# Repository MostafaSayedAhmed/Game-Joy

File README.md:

# Game-Joy
The Project is game console i call it Game Joy that contain two games: Snake Game and Jumping Game ( Like Google Dino)

The Project consist of 3 Part :
- Code :
it contain implementation of both jumping game and snake game where an external interrupt is used to start game at menu and an external button is used to switch between the 2 games

- Hardware Design :
The board is designed using Eagle with documentation about the function of each button

- Simulation:
The whole project is simulated using proteus which is used to check bugs and glitches

Components Used:
- ATMEGA328P
- LCD
- 4 Switches
- Battery
- one 220 ohm resistor

Skills Used :
- Problem Solving
- Coding

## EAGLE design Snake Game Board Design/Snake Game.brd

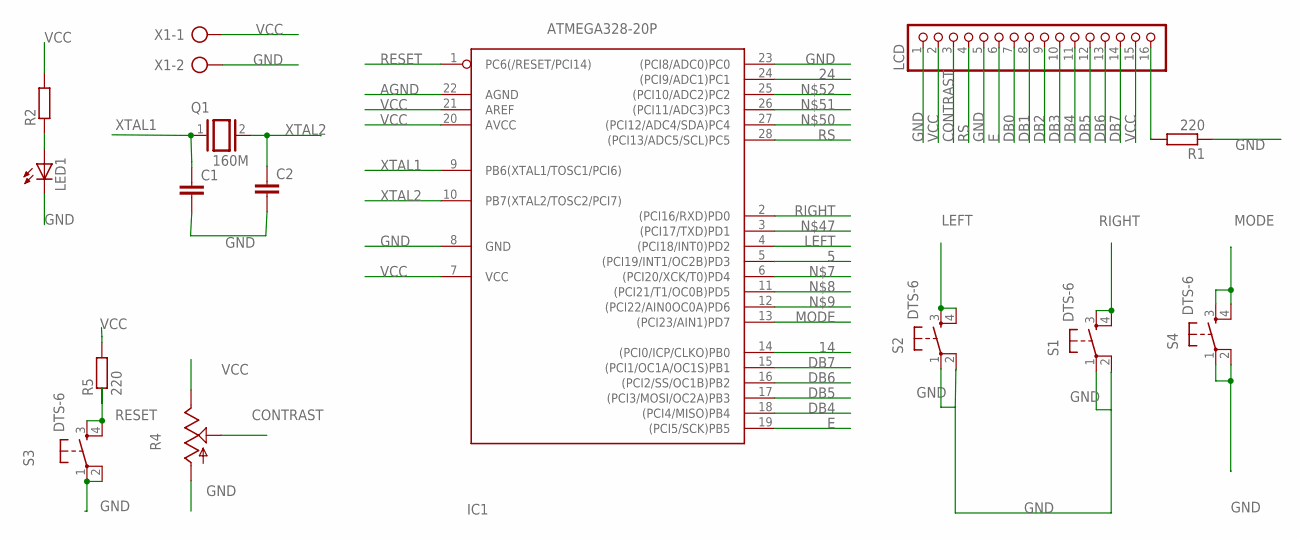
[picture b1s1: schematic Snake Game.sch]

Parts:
C1, C2: C2.5/2; C2.5-2
IC1: ATMEGA328-20P; DIL28-3
LCD: PINHD-1X16; 1X16
LED1: LED_LED3MM
Q1: 160M; QS
R1, R5: 220; 0204/7
R2: RCL_R-EU_0204/7; RCL_0204/7
R4: TRIM_US-B25P; B25P
S1, S2, S3, S4: DTS-6
X1: AK300/2

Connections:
5: IC1.5 ((PCI19/INT1/OC2B)PD3)
14: IC1.14 ((PCI0/ICP/CLKO)PB0)
24: IC1.24 ((PCI9/ADC1)PC1)
AGND: IC1.22 (AGND)
CONTRAST: LCD.3, R4.S
DB0: LCD.7
DB1: LCD.8
DB2: LCD.9
DB3: LCD.10
DB4: IC1.18 ((PCI4/MISO)PB4), LCD.11
DB5: IC1.17 ((PCI3/MOSI/OC2A)PB3), LCD.12
DB6: IC1.16 ((PCI2/SS/OC1B)PB2), LCD.13
DB7: IC1.15 ((PCI1/OC1A/OC1S)PB1), LCD.14
E: IC1.19 ((PCI5/SCK)PB5), LCD.6
GND: C1.2, C2.2, IC1.8 (GND), IC1.23 ((PCI8/ADC0)PC0), LCD.1, LCD.5, LED1.K (C), R1.1, R4.A, S1.1, S1.2, S2.1, S2.2, S3.1, S3.2, S4.1, S4.2, X1.2
LEFT: IC1.4 ((PCI18/INT0)PD2), S2.3, S2.4
MODE: IC1.13 ((PCI23/AIN1)PD7), S4.3, S4.4
unnamed: LCD.16, R1.2
unnamed: LED1.A, R2.1
RESET: IC1.1 (PC6(/RESET/PCI14)), R5.1, S3.3, S3.4
RIGHT: IC1.2 ((PCI16/RXD)PD0), S1.3, S1.4
RS: IC1.28 ((PCI13/ADC5/SCL)PC5), LCD.4
VCC: IC1.7 (VCC), IC1.20 (AVCC), IC1.21 (AREF), LCD.2, LCD.15, R2.2, R4.E, R5.2, X1.1
XTAL1: C1.1, IC1.9 (PB6(XTAL1/TOSC1/PCI6)), Q1.1
XTAL2: C2.1, IC1.10 (PB7(XTAL2/TOSC2/PCI7)), Q1.2

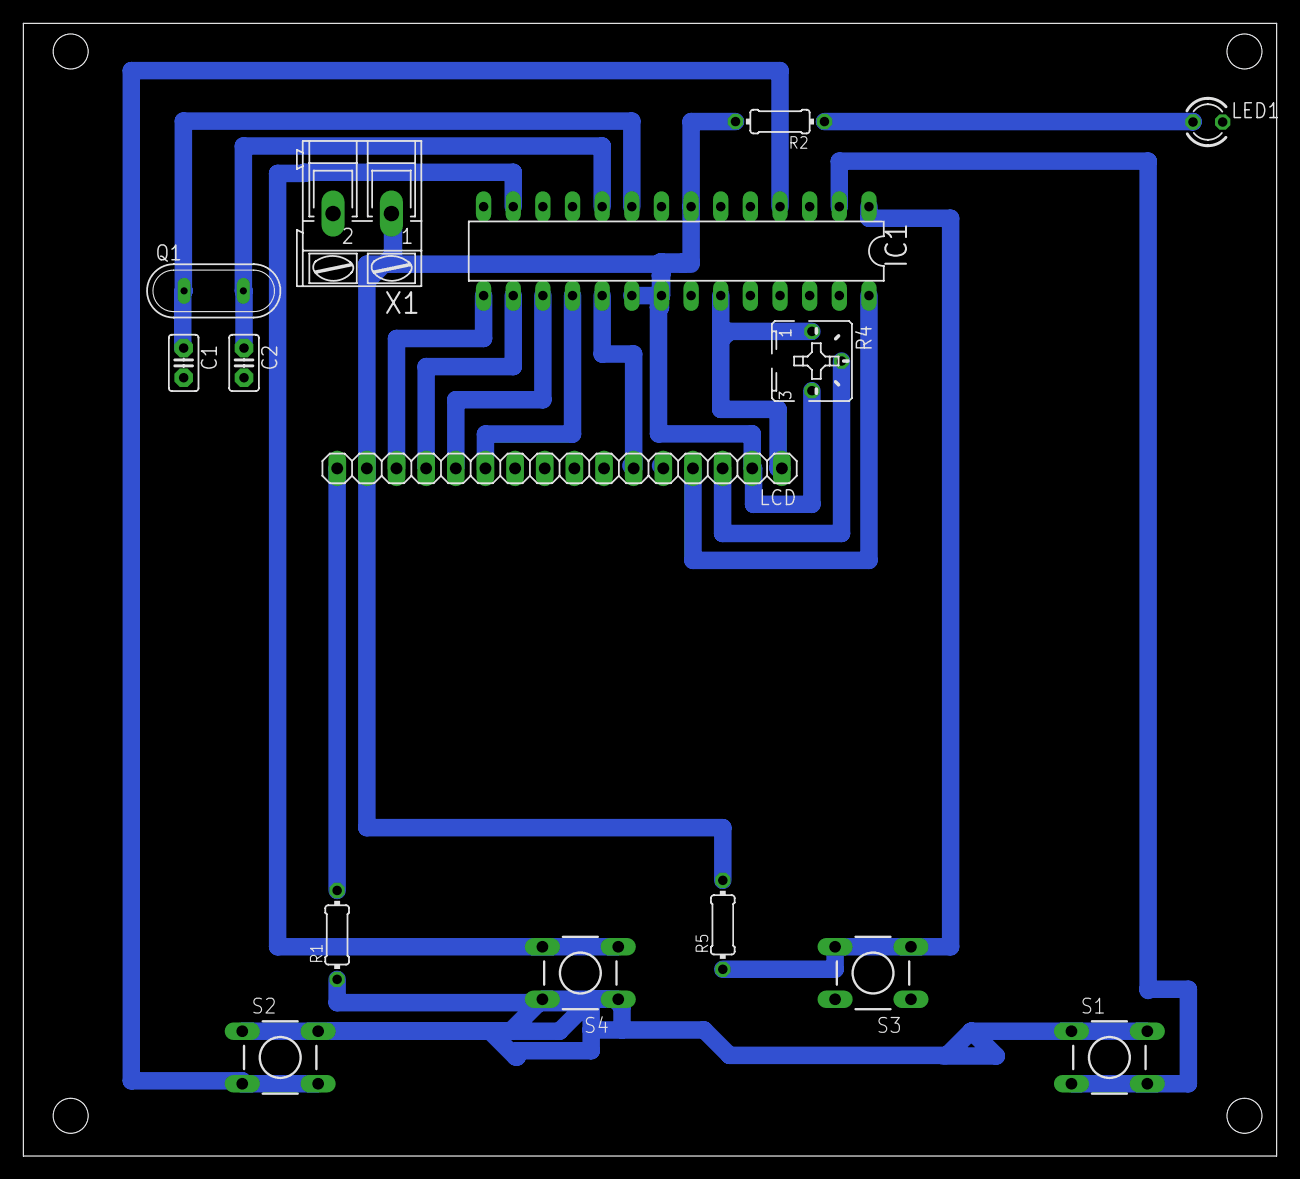
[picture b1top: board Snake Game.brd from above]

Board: 2 copper layers, 107.4 x 97.1 mm, 15 parts (0 on the bottom side), 17 nets.
